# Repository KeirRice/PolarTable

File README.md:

# PolarTable

A colletion of design, code and art that is my journey towards making a physical table with a polor plotting system build in.

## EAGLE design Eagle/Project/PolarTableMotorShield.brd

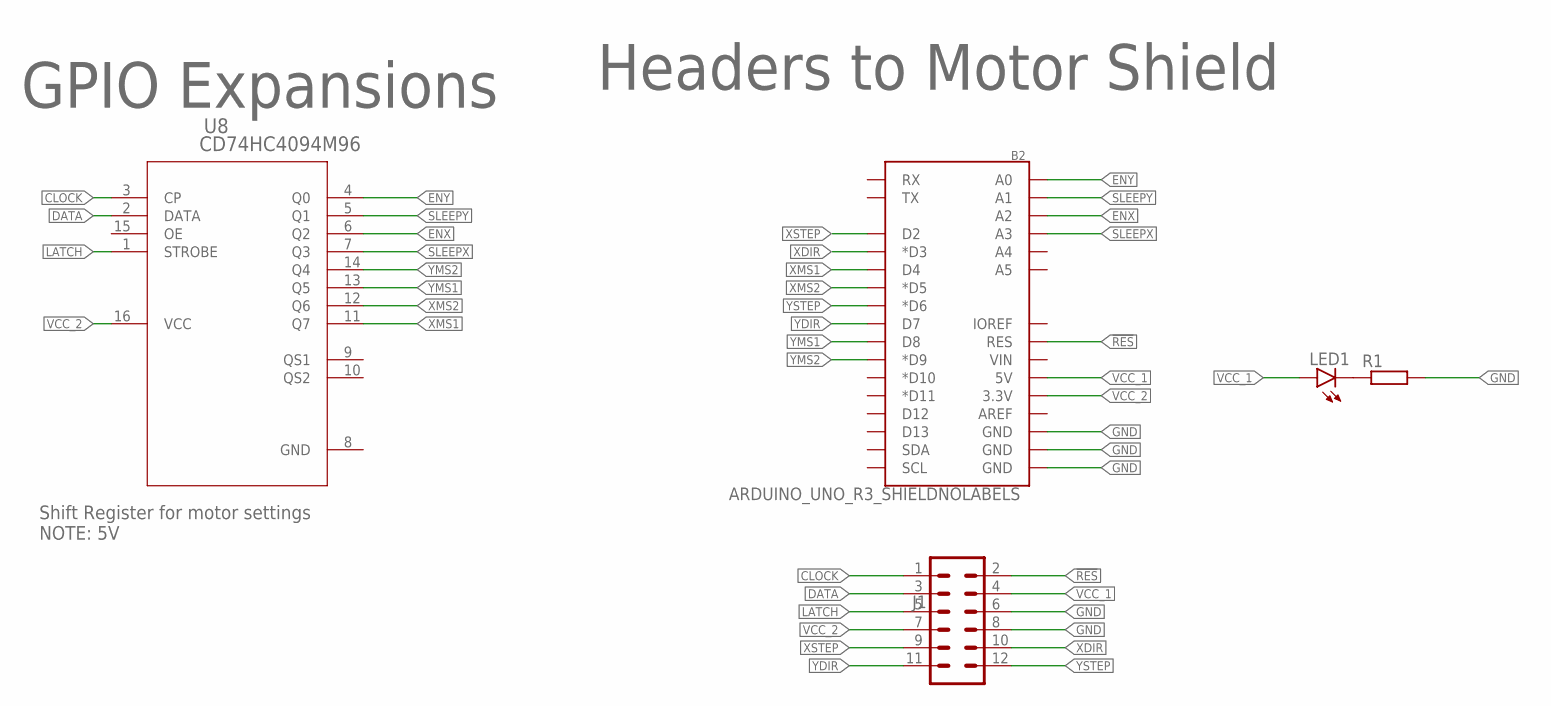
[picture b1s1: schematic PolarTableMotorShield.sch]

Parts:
B2: ARDUINO_UNO_R3_SHIELDNOLABELS; UNO_R3_SHIELD_NOLABELS
J1: CONN_06X21.24MM_RA_MALE; 2X6
LED1: LEDCHIPLED_0805; CHIPLED_0805
R1: R-EU_R0805; R0805
U8: CD74HC4094M96; D16

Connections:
!RES: B2.RES, J1.2
CLOCK: J1.1, U8.3 (CP)
DATA: J1.3, U8.2 (DATA)
ENX: B2.A2, U8.6 (Q2)
ENY: B2.A0, U8.4 (Q0)
GND: B2.GND@0 (GND), B2.GND@1 (GND), B2.GND@2 (GND), J1.6, J1.8, R1.2, U8.8 (GND)
LATCH: J1.5, U8.1 (STROBE)
unnamed: LED1.C, R1.1
SLEEPX: B2.A3, U8.7 (Q3)
SLEEPY: B2.A1, U8.5 (Q1)
VCC_1: B2.5V, J1.4, LED1.A
VCC_2: B2.3.3V, J1.7, U8.16 (VCC)
XDIR: B2.D3 (*D3), J1.10
XMS1: B2.D4, U8.11 (Q7)
XMS2: B2.D5 (*D5), U8.12 (Q6)
XSTEP: B2.D2, J1.9
YDIR: B2.D7, J1.11
YMS1: B2.D8, U8.13 (Q5)
YMS2: B2.D9 (*D9), U8.14 (Q4)
YSTEP: B2.D6 (*D6), J1.12

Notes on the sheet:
GPIO Expansions
Shift Register for motor settings NOTE: 5V
Headers to Motor Shield

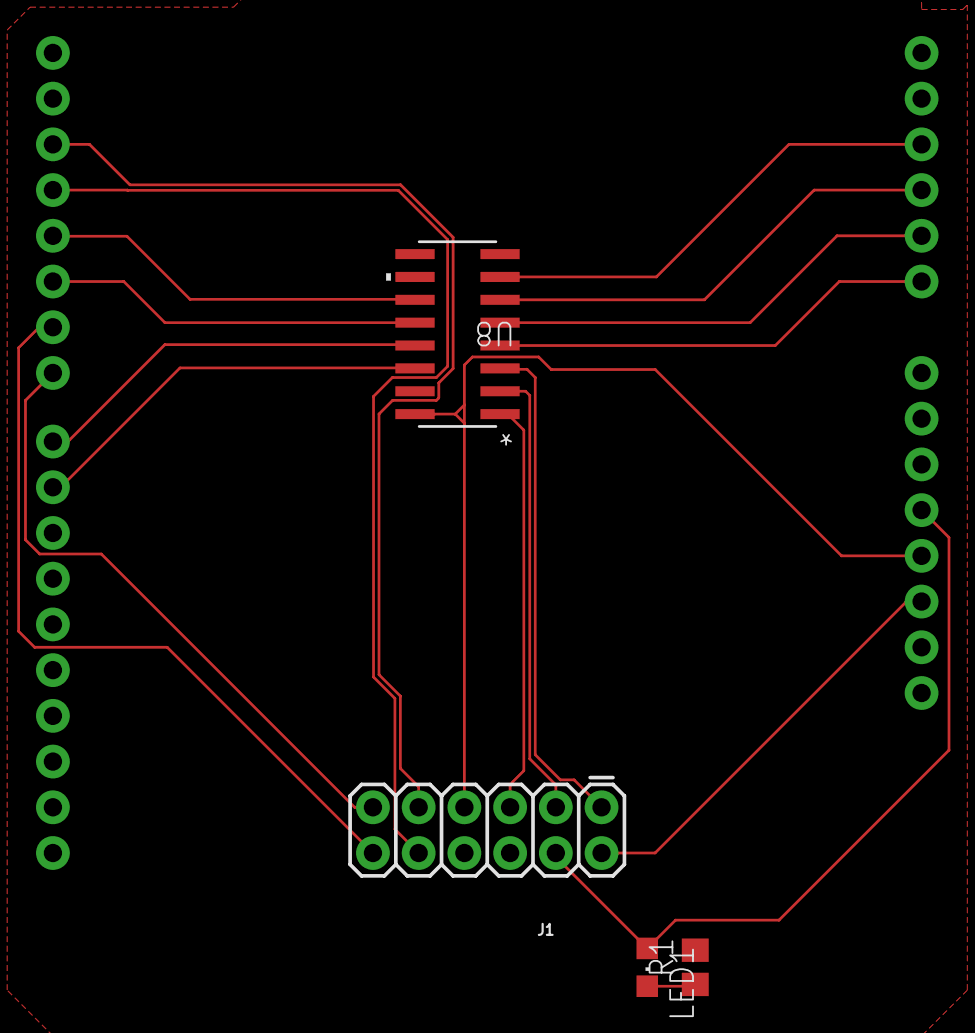
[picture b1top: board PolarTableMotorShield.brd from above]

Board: 2 copper layers, 5 parts (0 on the bottom side), 20 nets.

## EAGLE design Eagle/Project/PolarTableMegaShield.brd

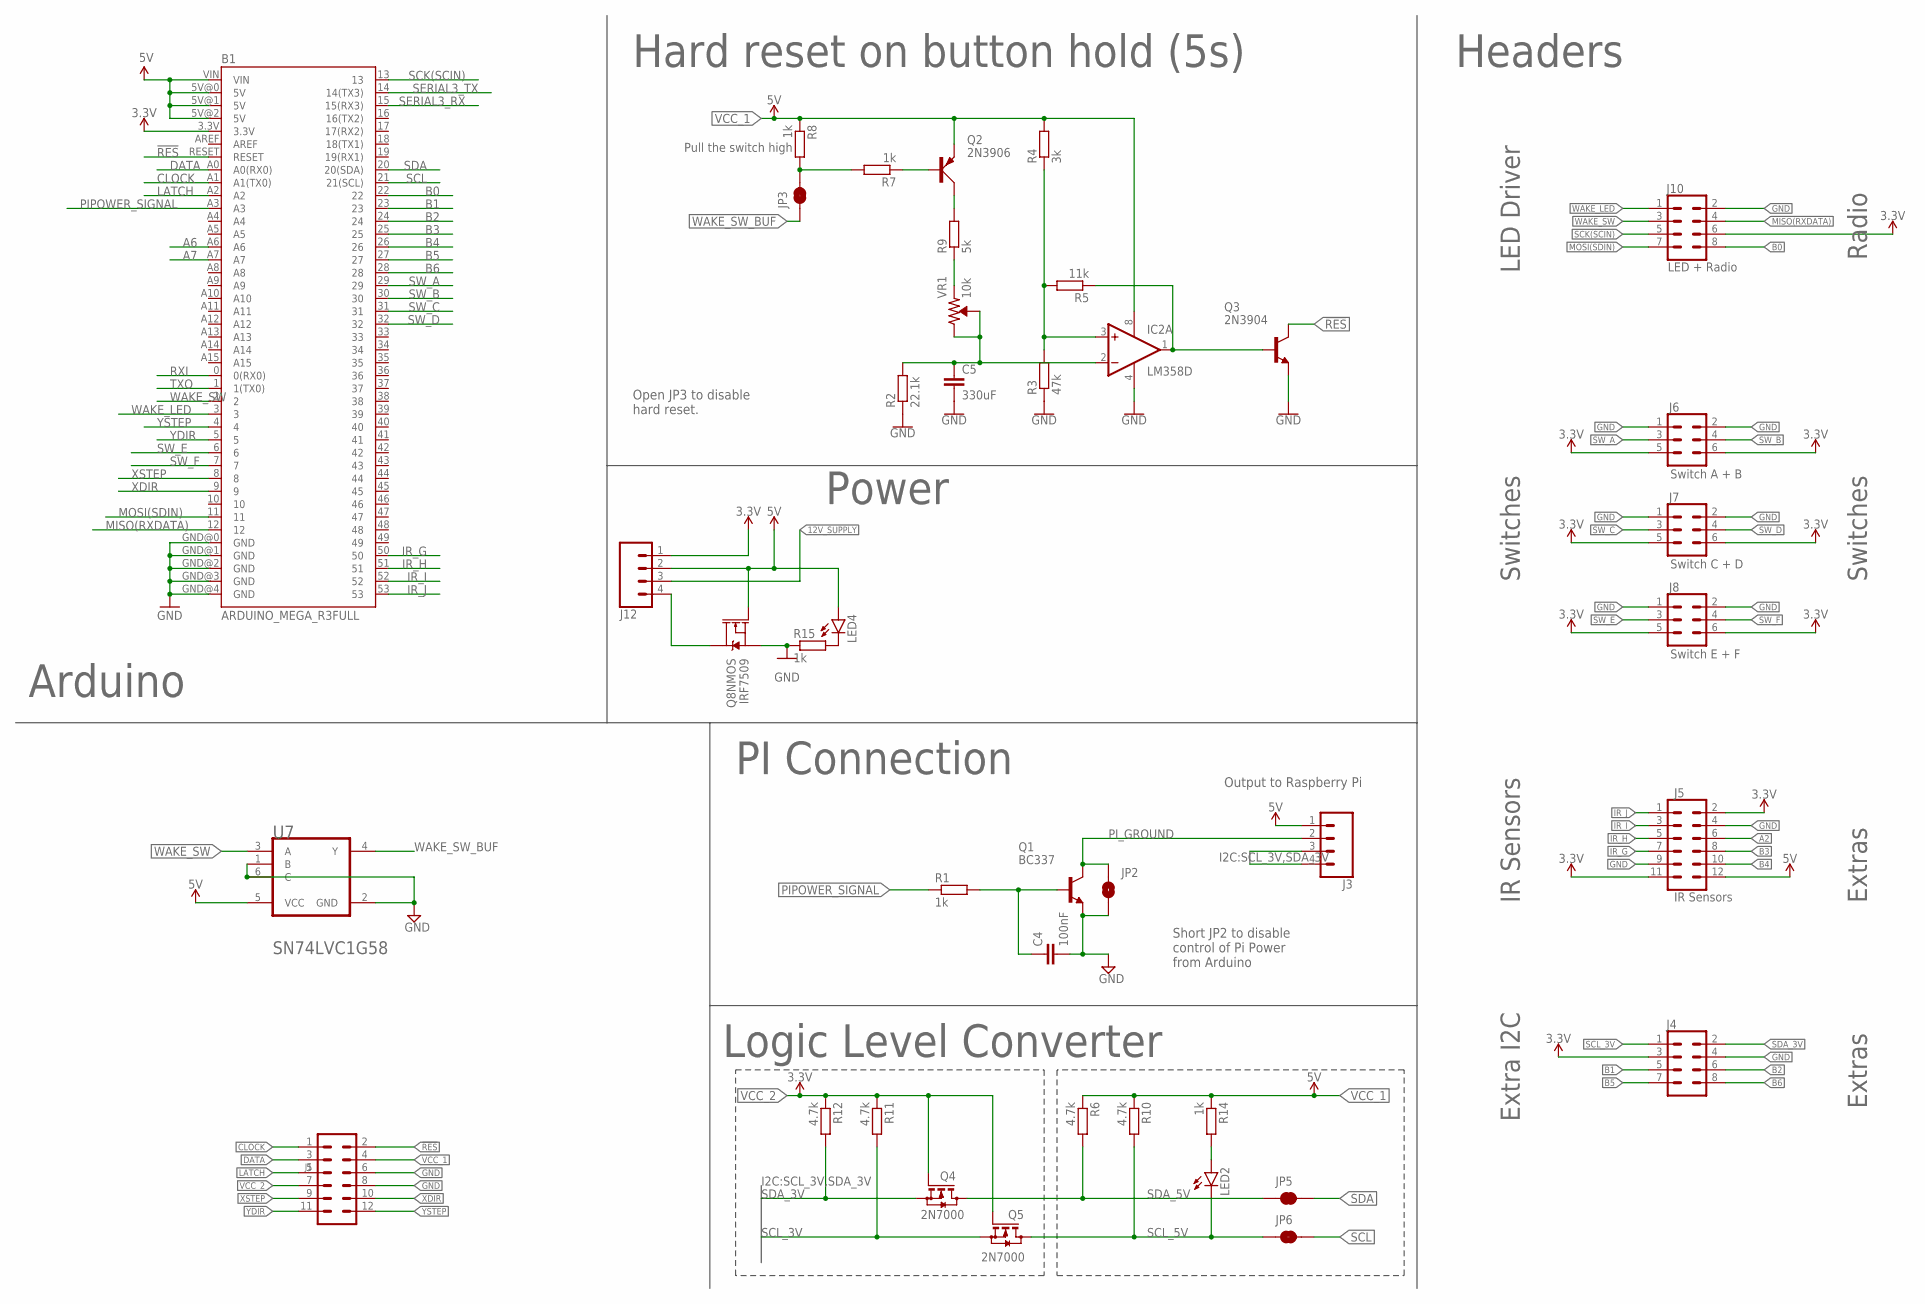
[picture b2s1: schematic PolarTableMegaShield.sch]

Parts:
B1: ARDUINO_MEGA_R3FULL; ARDUINO_MEGA
C4: 100nF; C0805
C5: 330uF; C0805
IC2: LM358D; SO08
J1: CONN_06X21.24MM_RA_MALE; 2X6
J3: Pi Connection; 1X04_1.24MM_RA_MALE
J4: CONN_04X22X4_1.24MM_RA_MALE; 2X4
J5: IR Sensors; 2X6
J6: Switch A + B; 2X3
J7: Switch C + D; 2X3
J8: Switch E + F; 2X3
J10: LED + Radio; 2X4
J12: CONN_04JST-PTH; JST-4-PTH
JP2: JUMPER-SMT_2_NO_SILK; SMT-JUMPER_2_NO_SILK
JP3: Enable Hold to Reset; SMT-JUMPER_2_NC_TRACE_SILK
JP5, JP6: JUMPER-SMT_2_NC_TRACE_NO-SILK; SMT-JUMPER_2_NC_TRACE_NO-SILK
LED2, LED4: LEDCHIP-LED0805; CHIP-LED0805
Q1: BC337; TO92
Q2: 2N3906; TO92D
Q3: 2N3904; TO92
Q4, Q5: 2N7000; TO92-
Q8: IRF7509; MSOP8
R1, R7, R8, R14, R15: 1k; M0805
R2: 22.1k; M0805
R3: 47k; M0805
R4: 3k; M0805
R5: 11k; M0805
R6, R10, R11, R12: 4.7k; M0805
R9: 5k; M0805
U7: Buffer; SOT363_PHILIPS
VR1: 10k; TRIMPOT-PTH-3386U

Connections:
12V_SUPPLY: J12.3
!RES: B1.RESET, J1.2, Q3.1 (C)
$N99: JP3.2, R7.2, R8.2
A2: J5.6
A6: B1.A6
A7: B1.A7
B0: B1.22, J10.8
B1: B1.23, J4.5
B2: B1.24, J4.6
B3: B1.25, J5.8
B4: B1.26, J5.10
B5: B1.27, J4.7
B6: B1.28, J4.8
CLOCK: B1.A1 (A1(TX0)), J1.1
COMP_OUT: IC2.1 (OUT), Q3.2 (B), R5.1
DATA: B1.A0 (A0(RX0)), J1.3
GND: B1.GND@0 (GND), B1.GND@1 (GND), B1.GND@2 (GND), B1.GND@3 (GND), B1.GND@4 (GND), C4.2, C5.2, IC2.4 (V-), J1.6, J1.8, J4.4, J5.4, J5.9, J6.1, J6.2, J7.1, J7.2, J8.1, J8.2, J10.2, JP2.2, Q1.1 (E), Q3.3 (E), Q8.1 (S), R2.1, R3.1, R15.1, U7.1 (B), U7.2 (GND), U7.6 (C)
IR_G: B1.50, J5.7
IR_H: B1.51, J5.5
IR_I: B1.52, J5.3
IR_J: B1.53, J5.1
LATCH: B1.A2, J1.5
MISO(RXDATA): B1.12, J10.4
MOSI(SDIN): B1.11, J10.7
unnamed: Q2.B, R7.1
unnamed: C4.1, Q1.2 (B), R1.2
unnamed: Q2.C, R9.2
unnamed: J12.4, Q8.7 (D), Q8.8 (D)
unnamed: IC2.3 (+IN), R3.2, R4.1, R5.2
unnamed: R9.1, VR1.1 (CCW)
unnamed: C5.1, IC2.2 (-IN), R2.2, VR1.2 (WIPER), VR1.3 (CW)
unnamed: LED4.C, R15.2
unnamed: LED2.A, R14.2
PIPOWER_SIGNAL: B1.A3, R1.1
PI_GROUND: J3.2, JP2.1, Q1.3 (C)
RXI: B1.0 (0(RX0))
SCK(SCIN): B1.13, J10.5
SCL: B1.21 (21(SCL)), JP6.2
SCL_3V: J3.3, J4.1, Q5.1 (S), R11.2
SCL_5V: JP6.1, LED2.C, Q5.3 (D), R10.2
SDA: B1.20 (20(SDA)), JP5.2
SDA_3V: J3.4, J4.2, Q4.1 (S), R12.2
SDA_5V: JP5.1, Q4.3 (D), R6.2
SERIAL3_RX: B1.15 (15(RX3))
SERIAL3_TX: B1.14 (14(TX3))
SW_A: B1.29, J6.3
SW_B: B1.30, J6.4
SW_C: B1.31, J7.3
SW_D: B1.32, J7.4
SW_E: B1.6, J8.3
SW_F: B1.7, J8.4
TXO: B1.1 (1(TX0))
VCC_1: B1.5V@0 (5V), B1.5V@1 (5V), B1.5V@2 (5V), B1.VIN, IC2.8 (V+), J1.4, J3.1, J5.12, J12.2, LED4.A, Q2.E, Q8.2 (G), R4.2, R6.1, R8.1, R10.1, R14.1, U7.5 (VCC)
VCC_2: B1.3.3V, J1.7, J4.3, J5.2, J5.11, J6.5, J6.6, J7.5, J7.6, J8.5, J8.6, J10.6, J12.1, Q4.2 (G), Q5.2 (G), R11.1, R12.1
WAKE_LED: B1.3, J10.1
WAKE_SW: B1.2, J10.3, U7.3 (A)
WAKE_SW_BUF: JP3.1, U7.4 (Y)
XDIR: B1.9, J1.10
XSTEP: B1.8, J1.9
YDIR: B1.5, J1.11
YSTEP: B1.4, J1.12

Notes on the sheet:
PI Connection
LED Driver
IR Sensors
Switches
Radio
Hard reset on button hold (5s)
Power
Logic Level Converter
Extras
Extra I2C
Arduino
Headers
Output to Raspberry Pi
Short JP2 to disable control of Pi Power from Arduino
Open JP3 to disable hard reset.

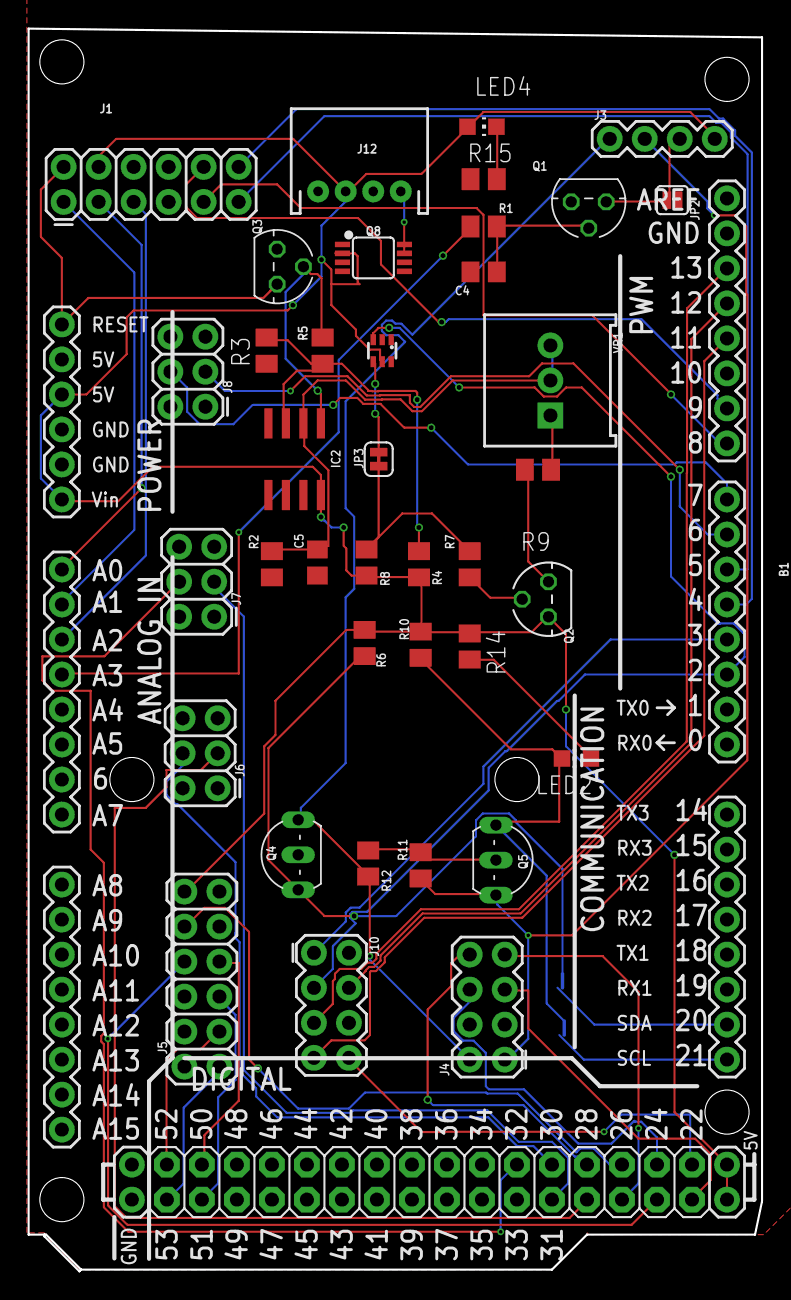
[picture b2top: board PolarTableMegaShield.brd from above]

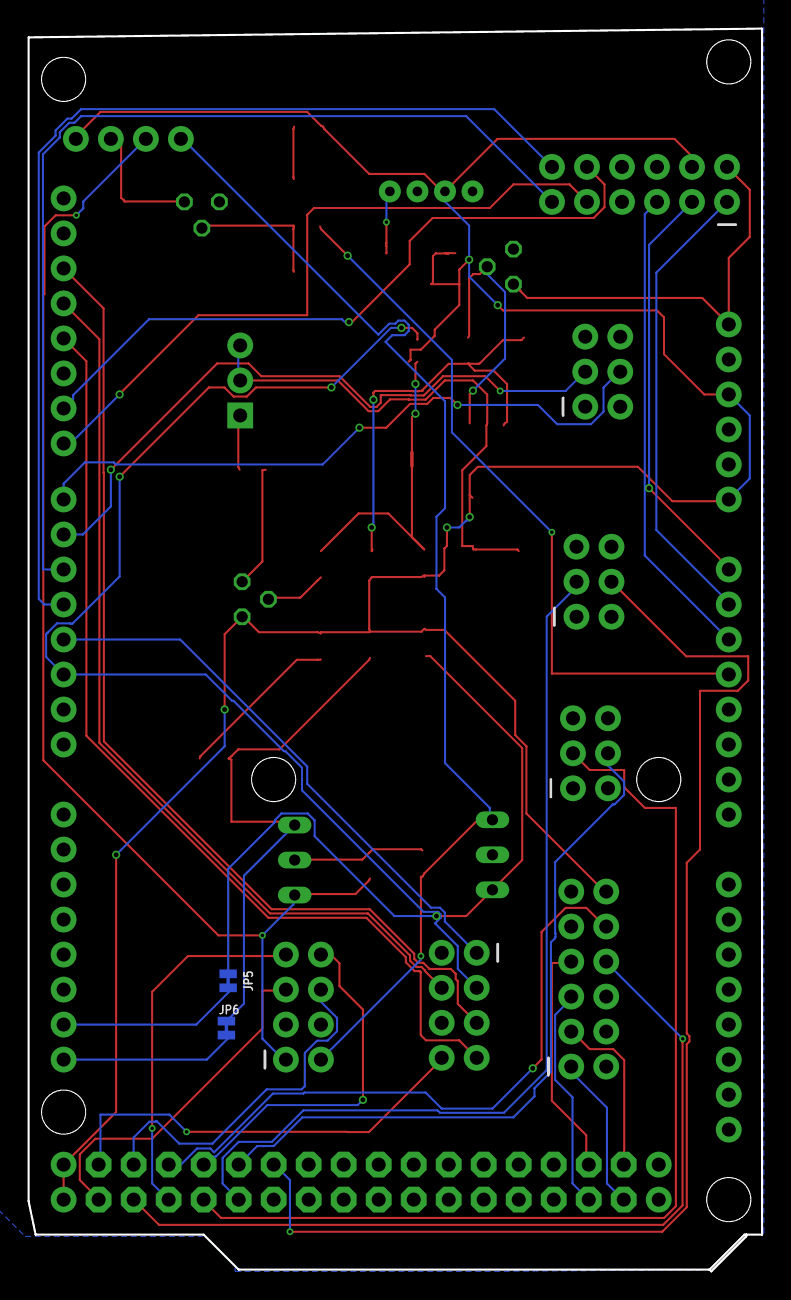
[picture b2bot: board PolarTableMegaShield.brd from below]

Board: 2 copper layers, 53.2 x 90.2 mm, 41 parts (2 on the bottom side), 53 nets.

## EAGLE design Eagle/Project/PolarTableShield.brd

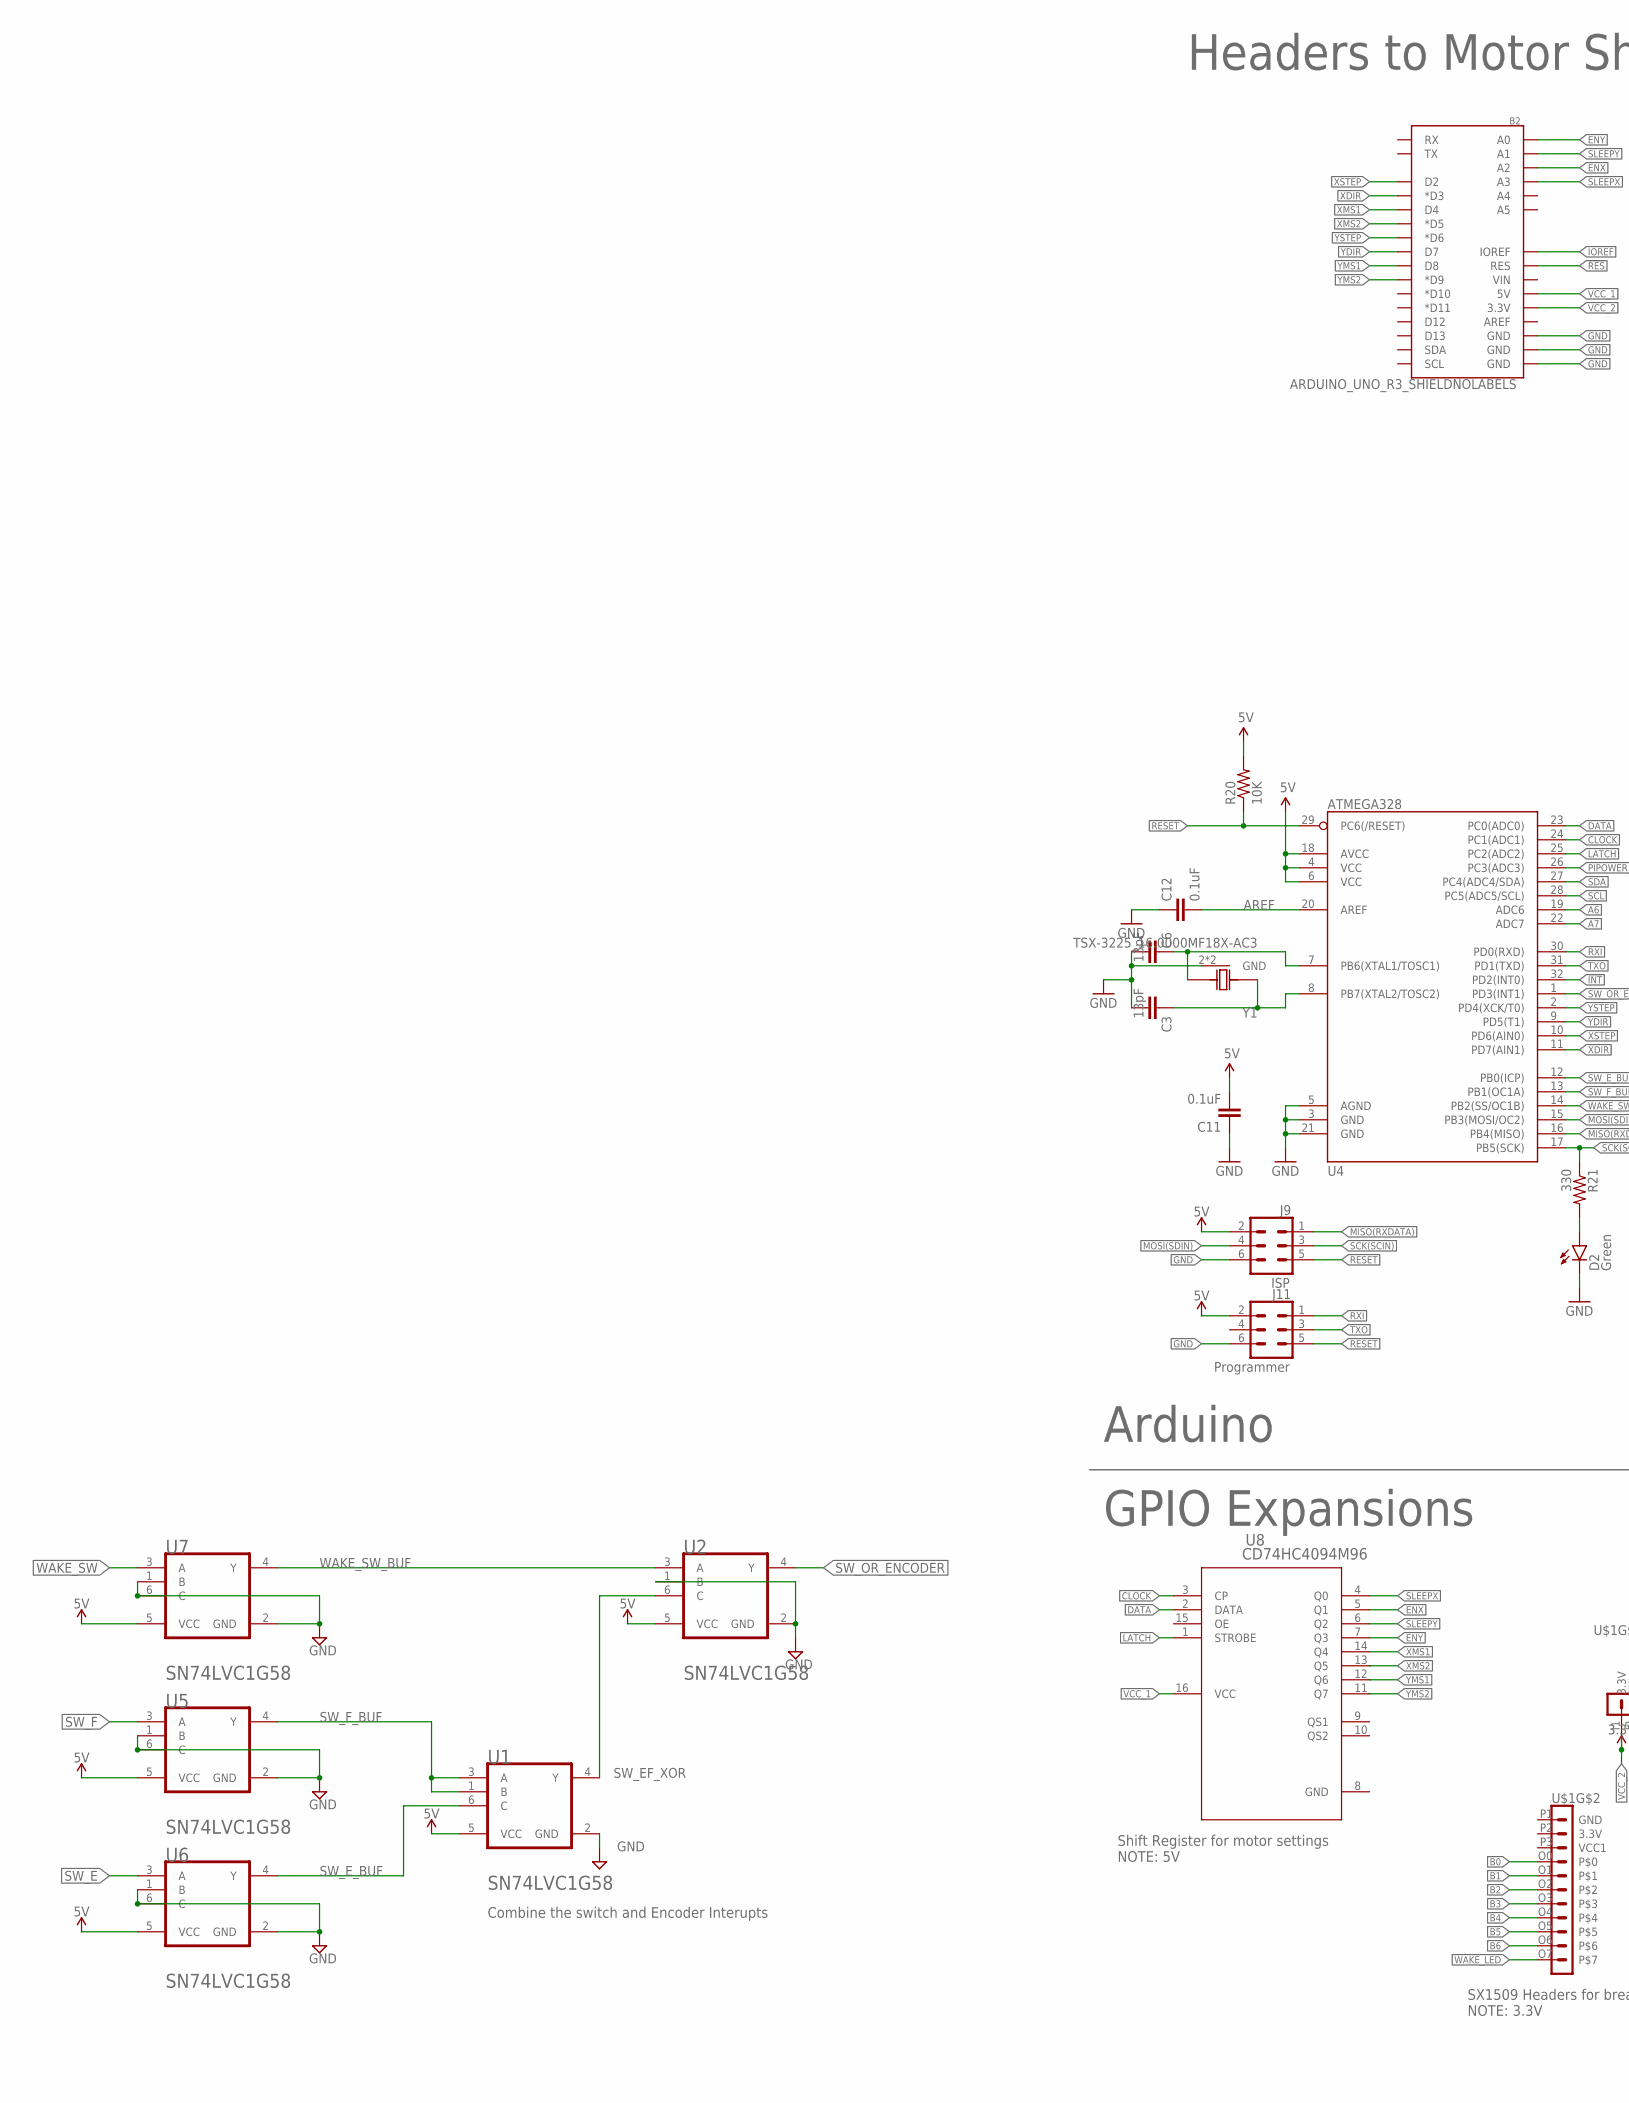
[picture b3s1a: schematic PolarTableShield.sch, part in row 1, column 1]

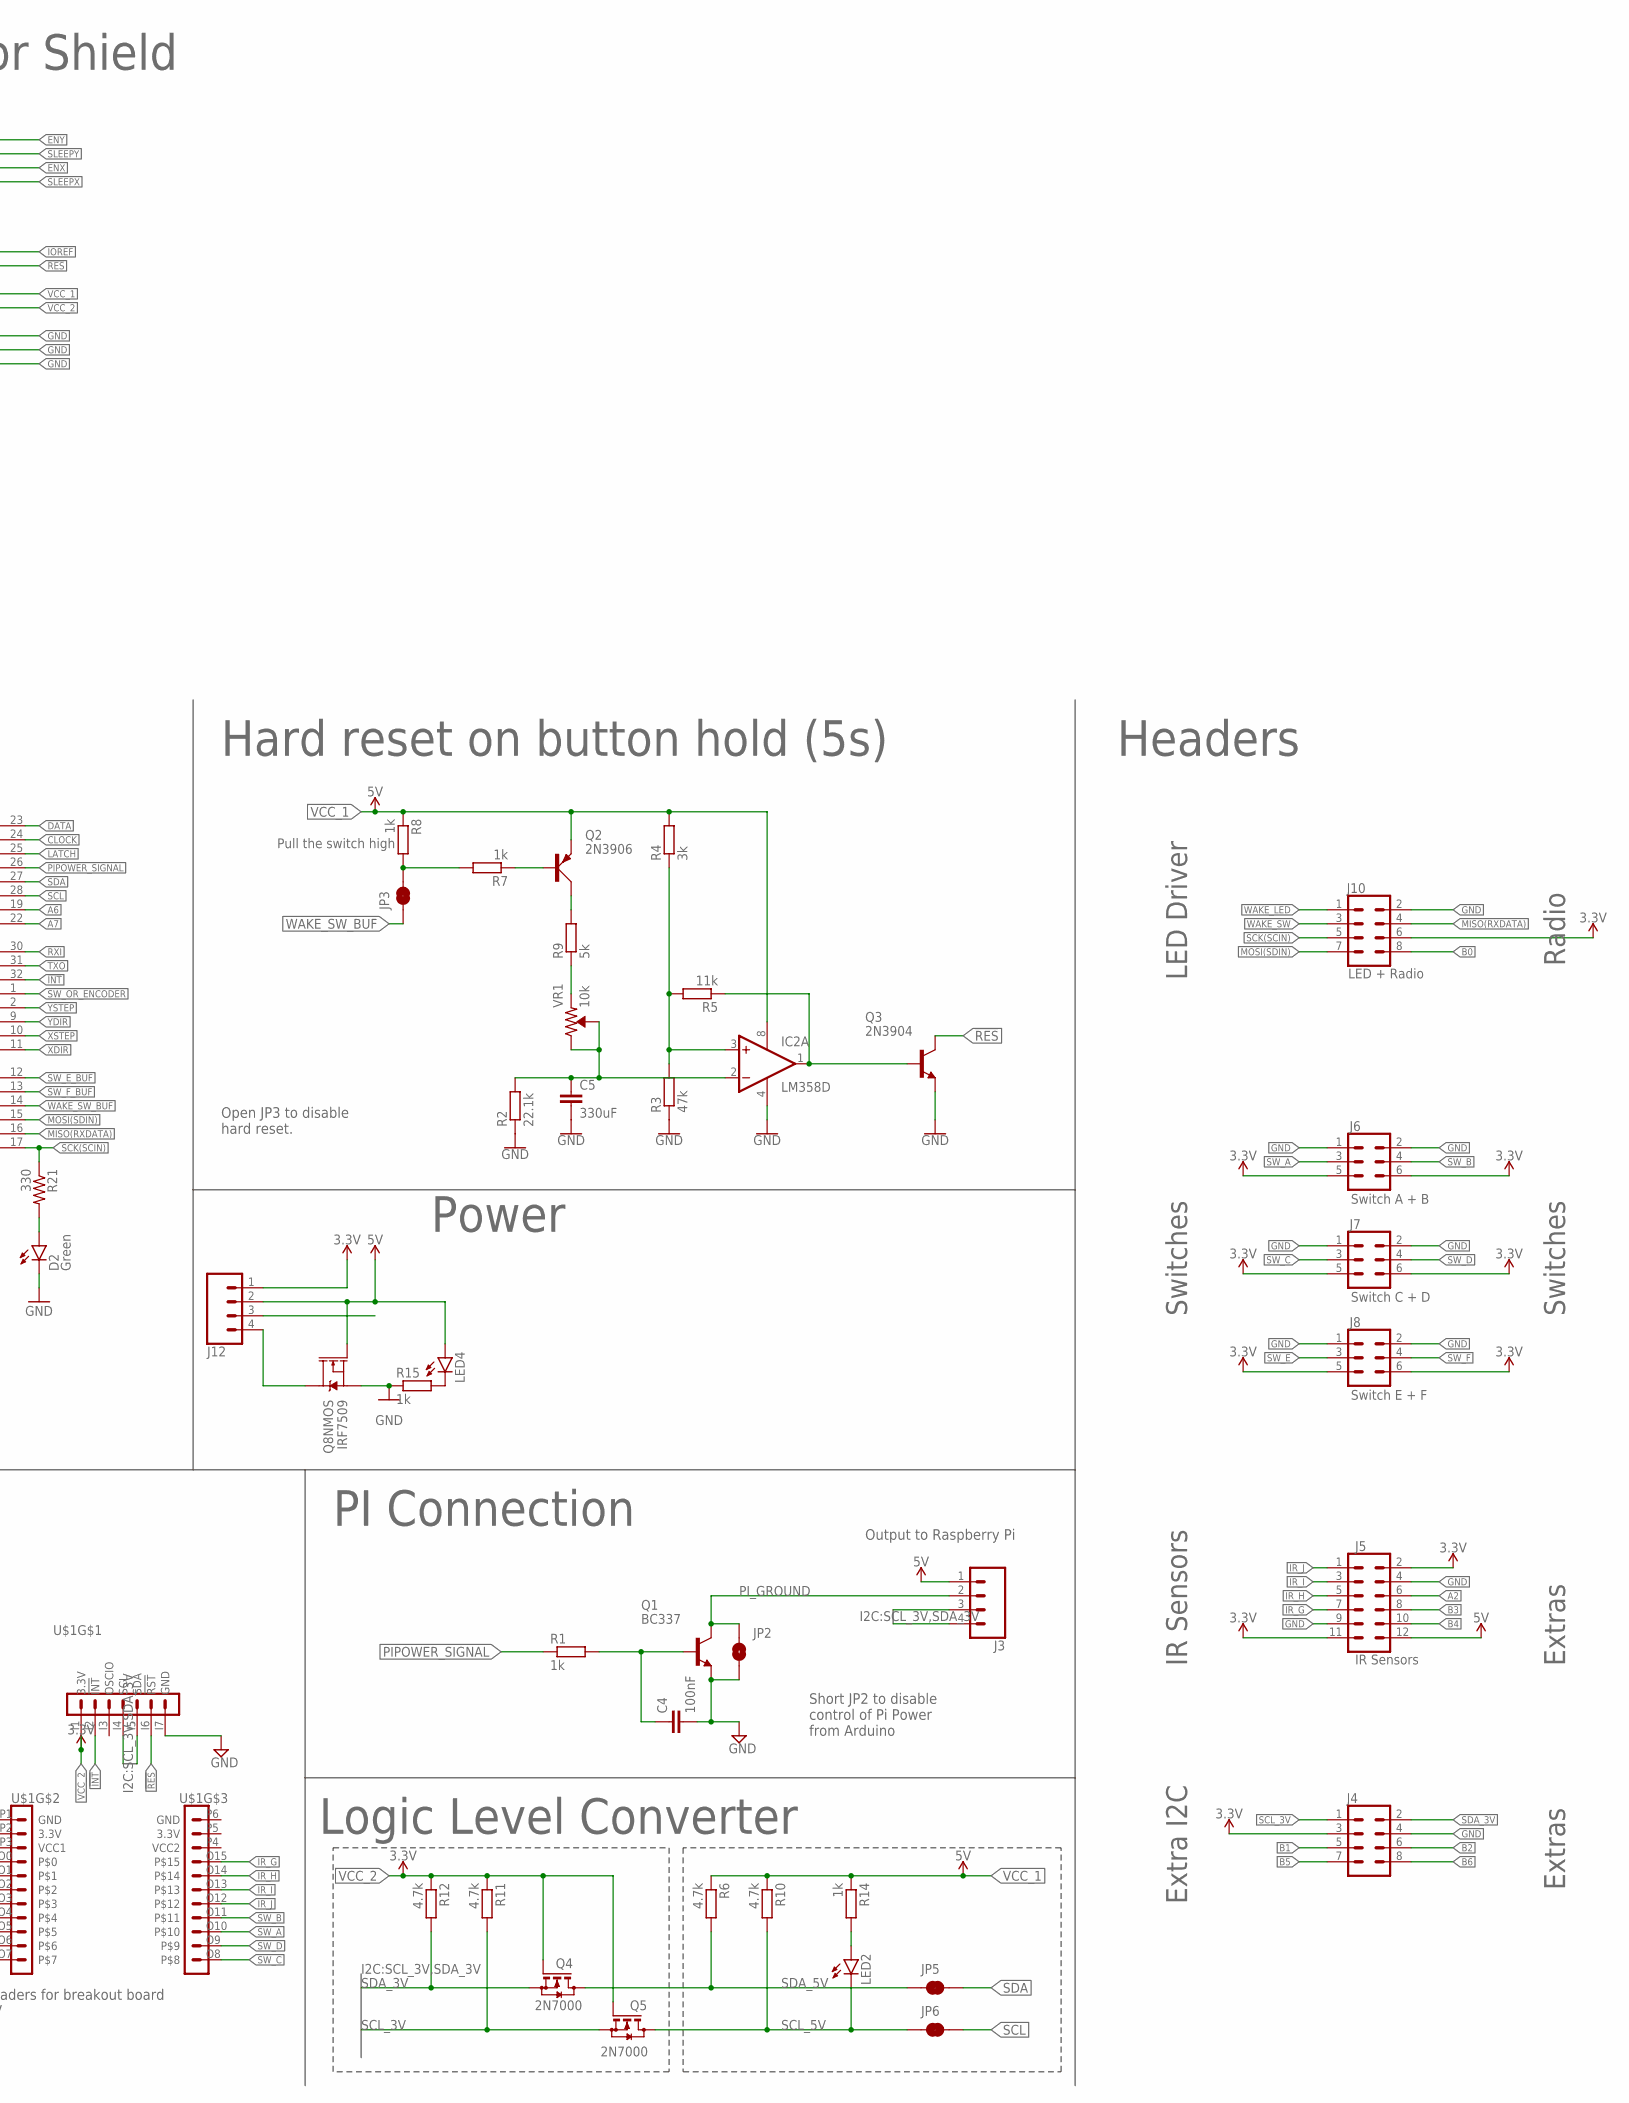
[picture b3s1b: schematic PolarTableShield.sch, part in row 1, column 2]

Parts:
B2: ARDUINO_UNO_R3_SHIELDNOLABELS; UNO_R3_SHIELD_NOLABELS
C3, C6: 13pF; 0603-CAP
C4: 100nF; C0805
C5: 330uF; C0805
C11, C12: 0.1uF; 0603-CAP
D2: Green; CHIP-LED0805
IC2: LM358D; SO08
J3: Pi Connection; 1X04_1.24MM_RA_MALE
J4: CONN_04X22X4_1.24MM_RA_MALE; 2X4
J5: IR Sensors; 2X6
J6: Switch A + B; 2X3
J7: Switch C + D; 2X3
J8: Switch E + F; 2X3
J9: ISP; 2X3-NS
J10: LED + Radio; 2X4
J11: Programmer; 2X3-NS
J12: CONN_04JST-PTH; JST-4-PTH
JP2: JUMPER-SMT_2_NO_SILK; SMT-JUMPER_2_NO_SILK
JP3: Enable Hold to Reset; SMT-JUMPER_2_NC_TRACE_SILK
JP5, JP6: JUMPER-SMT_2_NC_TRACE_NO-SILK; SMT-JUMPER_2_NC_TRACE_NO-SILK
LED2, LED4: LEDCHIP-LED0805; CHIP-LED0805
Q1: BC337; TO92
Q2: 2N3906; TO92D
Q3: 2N3904; TO92
Q4, Q5: 2N7000; TO92-
Q8: IRF7509; MSOP8
R1, R7, R8, R14, R15: 1k; M0805
R2: 22.1k; M0805
R3: 47k; M0805
R4: 3k; M0805
R5: 11k; M0805
R6, R10, R11, R12: 4.7k; M0805
R9: 5k; M0805
R20: 10K; 0603-RES
R21: 330; 0603-RES
U1: XOR; SOT363_PHILIPS
U2: OR; SOT363_PHILIPS
U4: ATMEGA328; TQFP32-08
U5, U6, U7: Buffer; SOT363_PHILIPS
U8: CD74HC4094M96; D16
U$1: SX1509
VR1: 10k; TRIMPOT-PTH-3386U
Y1: TSX-3225_16.0000MF18X-AC3; XTAL_TSX-3225_16.0000MF18X-AC3

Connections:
12V_SUPPLY: J12.3
!INT: U4.32 (PD2(INT0)), U$1.I2 (!INT)
!RES: B2.RES, Q3.1 (C), U$1.I6 (!RST)
$N99: JP3.2, R7.2, R8.2
A2: J5.6
A6: U4.19 (ADC6)
A7: U4.22 (ADC7)
AREF: C12.2, U4.20 (AREF)
B0: J10.8, U$1.O0
B1: J4.5, U$1.O1
B2: J4.6, U$1.O2
B3: J5.8, U$1.O3
B4: J5.10, U$1.O4
B5: J4.7, U$1.O5
B6: J4.8, U$1.O6
CLOCK: U4.24 (PC1(ADC1)), U8.3 (CP)
COMP_OUT: IC2.1 (OUT), Q3.2 (B), R5.1
DATA: U4.23 (PC0(ADC0)), U8.2 (DATA)
ENX: B2.A2, U8.5 (Q1)
ENY: B2.A0, U8.7 (Q3)
GND: B2.GND@0 (GND), B2.GND@1 (GND), B2.GND@2 (GND), C3.2, C4.2, C5.2, C6.2, C11.1, C12.1, D2.C, IC2.4 (V-), J4.4, J5.4, J5.9, J6.1, J6.2, J7.1, J7.2, J8.1, J8.2, J9.6, J10.2, J11.6, JP2.2, Q1.1 (E), Q3.3 (E), Q8.1 (S), R2.1, R3.1, R15.1, U1.2 (GND), U2.1 (B), U2.2 (GND), U4.3 (GND), U4.5 (AGND), U4.21 (GND), U5.1 (B), U5.2 (GND), U5.6 (C), U6.1 (B), U6.2 (GND), U6.6 (C), U7.1 (B), U7.2 (GND), U7.6 (C), U8.8 (GND), U$1.I7 (GND), Y1.2 (GND), Y1.4 (GND)
IOREF: B2.IOREF
IR_G: J5.7, U$1.O15
IR_H: J5.5, U$1.O14
IR_I: J5.3, U$1.O13
IR_J: J5.1, U$1.O12
LATCH: U4.25 (PC2(ADC2)), U8.1 (STROBE)
MISO(RXDATA): J9.1, J10.4, U4.16 (PB4(MISO))
MOSI(SDIN): J9.4, J10.7, U4.15 (PB3(MOSI/OC2))
unnamed: Q2.B, R7.1
unnamed: C4.1, Q1.2 (B), R1.2
unnamed: Q2.C, R9.2
unnamed: J12.4, Q8.7 (D), Q8.8 (D)
unnamed: IC2.3 (+IN), R3.2, R4.1, R5.2
unnamed: R9.1, VR1.1 (CCW)
unnamed: C3.1, U4.8 (PB7(XTAL2/TOSC2)), Y1.1
unnamed: C5.1, IC2.2 (-IN), R2.2, VR1.2 (WIPER), VR1.3 (CW)
unnamed: LED4.C, R15.2
unnamed: LED2.A, R14.2
unnamed: D2.A, R21.2
unnamed: C6.1, U4.7 (PB6(XTAL1/TOSC1)), Y1.3
PIPOWER_SIGNAL: R1.1, U4.26 (PC3(ADC3))
PI_GROUND: J3.2, JP2.1, Q1.3 (C)
RESET: J9.5, J11.5, R20.1, U4.29 (PC6(/RESET))
RXI: J11.1, U4.30 (PD0(RXD))
SCK(SCIN): J9.3, J10.5, R21.1, U4.17 (PB5(SCK))
SCL: JP6.2, U4.28 (PC5(ADC5/SCL))
SCL_3V: J3.3, J4.1, Q5.1 (S), R11.2, U$1.I4 (SCL)
SCL_5V: JP6.1, LED2.C, Q5.3 (D), R10.2
SDA: JP5.2, U4.27 (PC4(ADC4/SDA))
SDA_3V: J3.4, J4.2, Q4.1 (S), R12.2, U$1.I5 (SDA)
SDA_5V: JP5.1, Q4.3 (D), R6.2
SLEEPX: B2.A3, U8.4 (Q0)
SLEEPY: B2.A1, U8.6 (Q2)
SW_A: J6.3, U$1.O10
SW_B: J6.4, U$1.O11
SW_C: J7.3, U$1.O8
SW_D: J7.4, U$1.O9
SW_E: J8.3, U6.3 (A)
SW_EF_XOR: U1.4 (Y), U2.6 (C)
SW_E_BUF: U1.6 (C), U4.12 (PB0(ICP)), U6.4 (Y)
SW_F: J8.4, U5.3 (A)
SW_F_BUF: U1.1 (B), U1.3 (A), U4.13 (PB1(OC1A)), U5.4 (Y)
SW_OR_ENCODER: U2.4 (Y), U4.1 (PD3(INT1))
TXO: J11.3, U4.31 (PD1(TXD))
VCC_1: B2.5V, C11.2, IC2.8 (V+), J3.1, J5.12, J9.2, J11.2, J12.2, LED4.A, Q2.E, Q8.2 (G), R4.2, R6.1, R8.1, R10.1, R14.1, R20.2, U1.5 (VCC), U2.5 (VCC), U4.4 (VCC), U4.6 (VCC), U4.18 (AVCC), U5.5 (VCC), U6.5 (VCC), U7.5 (VCC), U8.16 (VCC)
VCC_2: B2.3.3V, J4.3, J5.2, J5.11, J6.5, J6.6, J7.5, J7.6, J8.5, J8.6, J10.6, J12.1, Q4.2 (G), Q5.2 (G), R11.1, R12.1, U$1.I1 (3.3V)
WAKE_LED: J10.1, U$1.O7
WAKE_SW: J10.3, U7.3 (A)
WAKE_SW_BUF: JP3.1, U2.3 (A), U4.14 (PB2(SS/OC1B)), U7.4 (Y)
XDIR: B2.D3 (*D3), U4.11 (PD7(AIN1))
XMS1: B2.D4, U8.14 (Q4)
XMS2: B2.D5 (*D5), U8.13 (Q5)
XSTEP: B2.D2, U4.10 (PD6(AIN0))
YDIR: B2.D7, U4.9 (PD5(T1))
YMS1: B2.D8, U8.12 (Q6)
YMS2: B2.D9 (*D9), U8.11 (Q7)
YSTEP: B2.D6 (*D6), U4.2 (PD4(XCK/T0))

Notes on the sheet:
PI Connection
LED Driver
IR Sensors
Switches
Radio
Hard reset on button hold (5s)
GPIO Expansions
Shift Register for motor settings NOTE: 5V
Power
Logic Level Converter
Extras
Extra I2C
Arduino
Headers to Motor Shield
SX1509 Headers for breakout board NOTE: 3.3V
Headers
Output to Raspberry Pi
Short JP2 to disable control of Pi Power from Arduino
Open JP3 to disable hard reset.
Combine the switch and Encoder Interupts

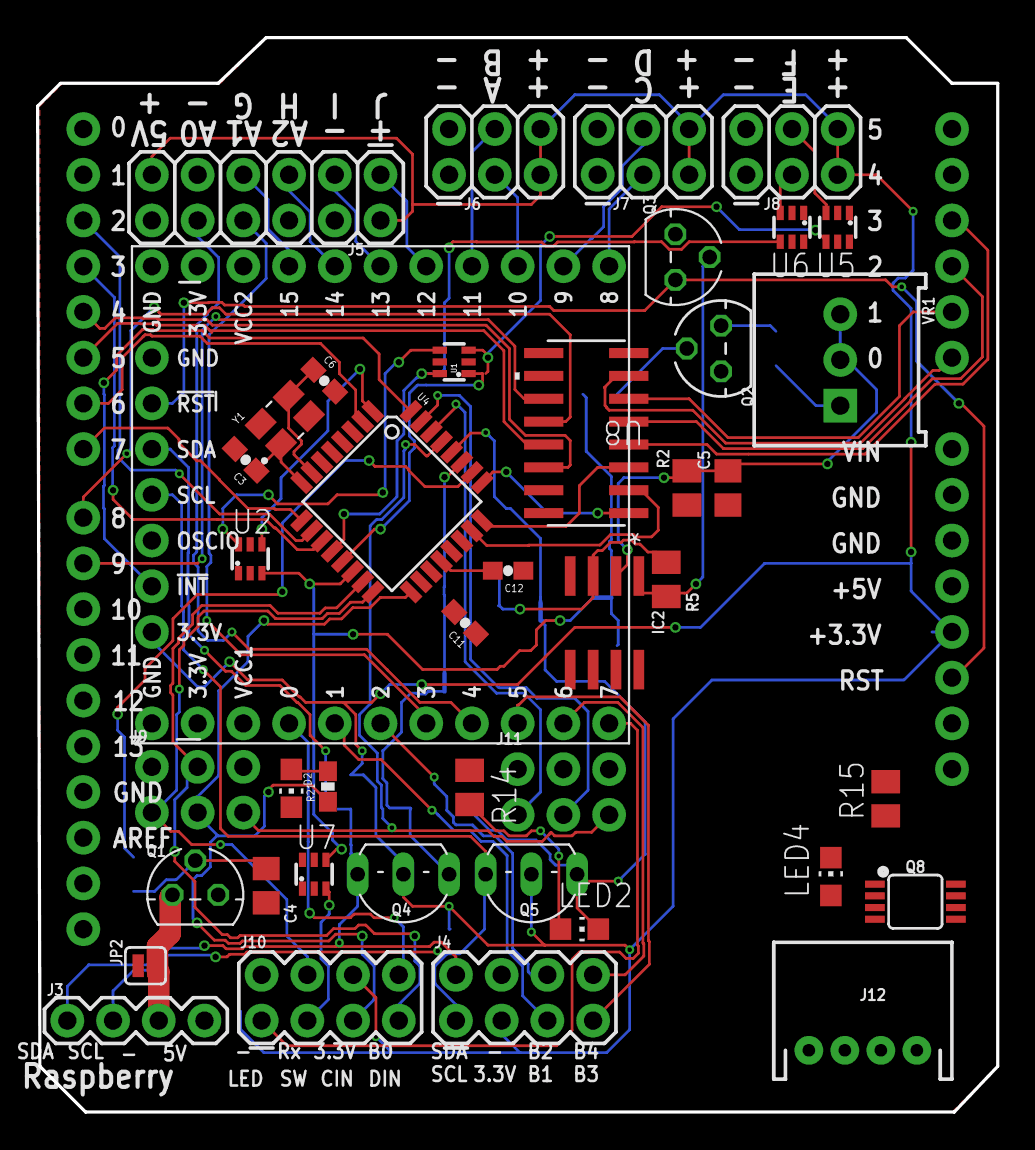
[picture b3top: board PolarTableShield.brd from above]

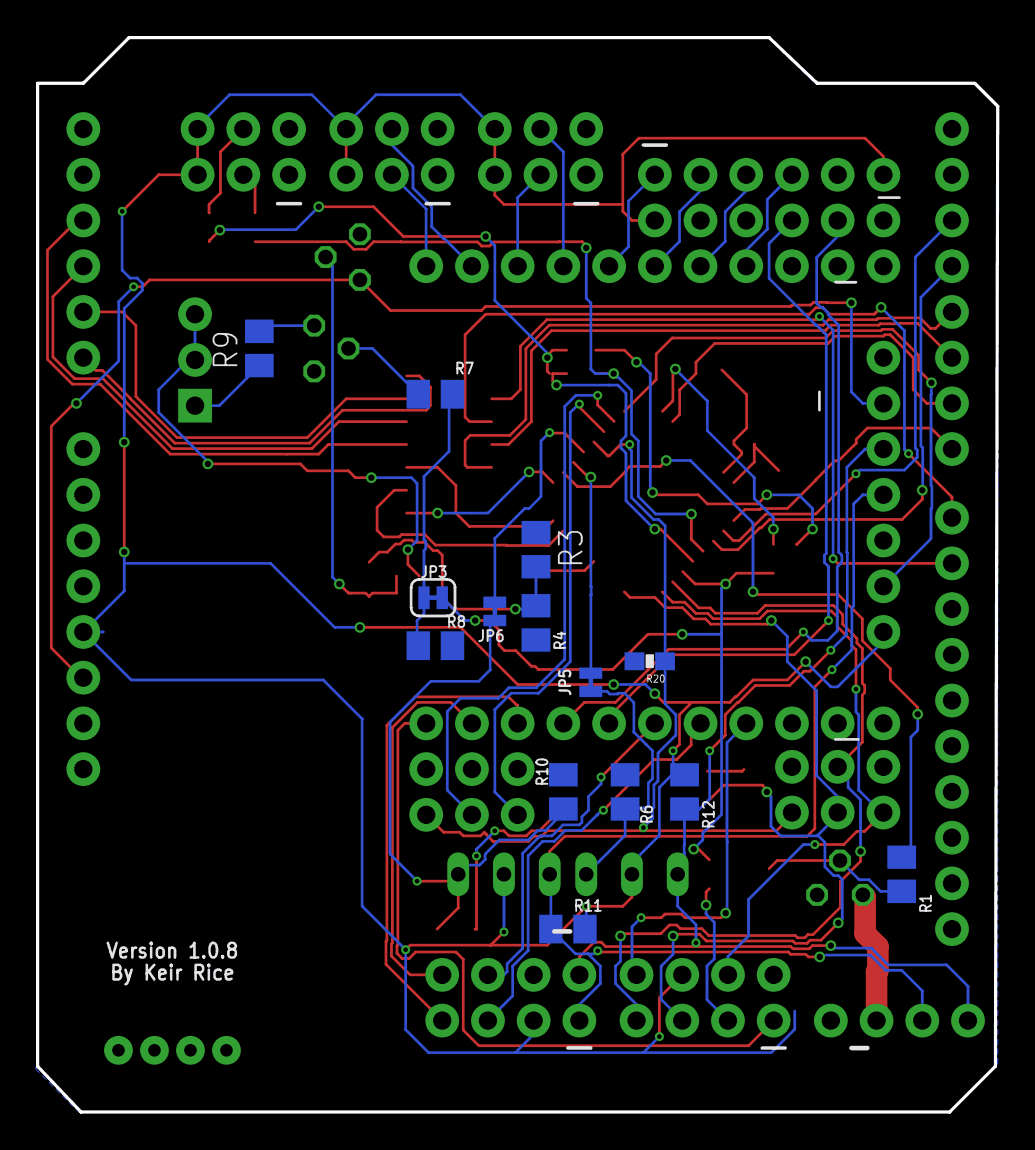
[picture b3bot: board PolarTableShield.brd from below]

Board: 2 copper layers, 53.3 x 59.7 mm, 58 parts (14 on the bottom side), 73 nets.

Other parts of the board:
U$3: TRI_LOGO_BOTTOM_5MM

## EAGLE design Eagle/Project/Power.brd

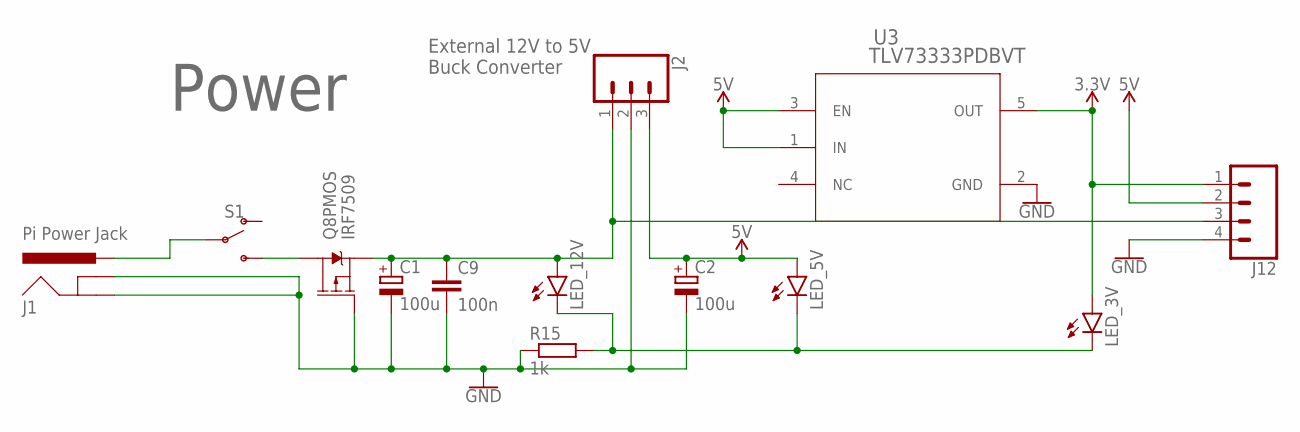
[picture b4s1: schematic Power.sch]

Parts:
C1, C2: 100u; E2-5
C9: 100n; C0805
J1: Pi Power Jack; POWER_JACK_PTH_BREAD
J2: Header - Right angled, female; 1X03
J12: CONN_04JST-PTH; JST-4-PTH
LED_3V, LED_5V, LED_12V: LEDCHIP-LED0805; CHIP-LED0805
Q8: IRF7509; MSOP8
R15: 1k; M0805
S1: SWITCH-SPDT-PTH-11.6X4.0MM; SWITCH_SPDT_PTH_11.6X4.0MM
U3: TLV73333PDBVT; DBV5

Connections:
12V_SUPPLY: C1.+, C9.1, J2.1, J12.3, LED_12V.A, Q8.3 (S)
GND: C1.-, C2.-, C9.2, J1.GND, J1.GNDBREAK, J2.2, J12.4, Q8.4 (G), R15.1, U3.2 (GND)
unnamed: Q8.5 (D), Q8.6 (D), S1.3 (S)
unnamed: J1.PWR, S1.2
unnamed: LED_3V.C, LED_5V.C, LED_12V.C, R15.2
VCC_1: C2.+, J2.3, J12.2, LED_5V.A, U3.1 (IN), U3.3 (EN)
VCC_2: J12.1, LED_3V.A, U3.5 (OUT)

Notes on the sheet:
Power
External 12V to 5V Buck Converter

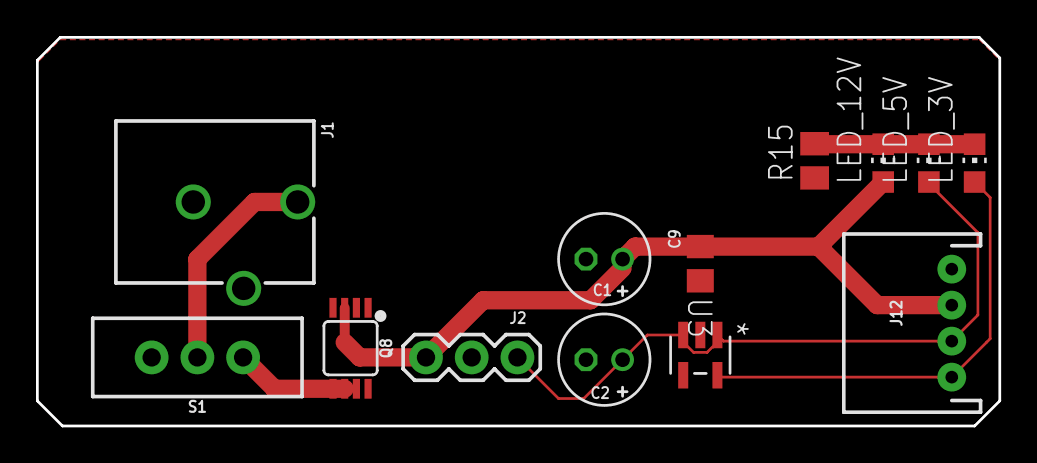
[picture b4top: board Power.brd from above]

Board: 2 copper layers, 53.5 x 21.6 mm, 13 parts (0 on the bottom side), 7 nets.

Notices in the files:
parts and their libraries:
SparkFun-Connectors: Licensing: Creative Commons ShareAlike 4.0 International - https://creativecommons.org/licenses/by-sa/4.0
SparkFun-Connectors: Licensing: CC v3.0 Share-Alike You are welcome to use this library for commercial purposes.
